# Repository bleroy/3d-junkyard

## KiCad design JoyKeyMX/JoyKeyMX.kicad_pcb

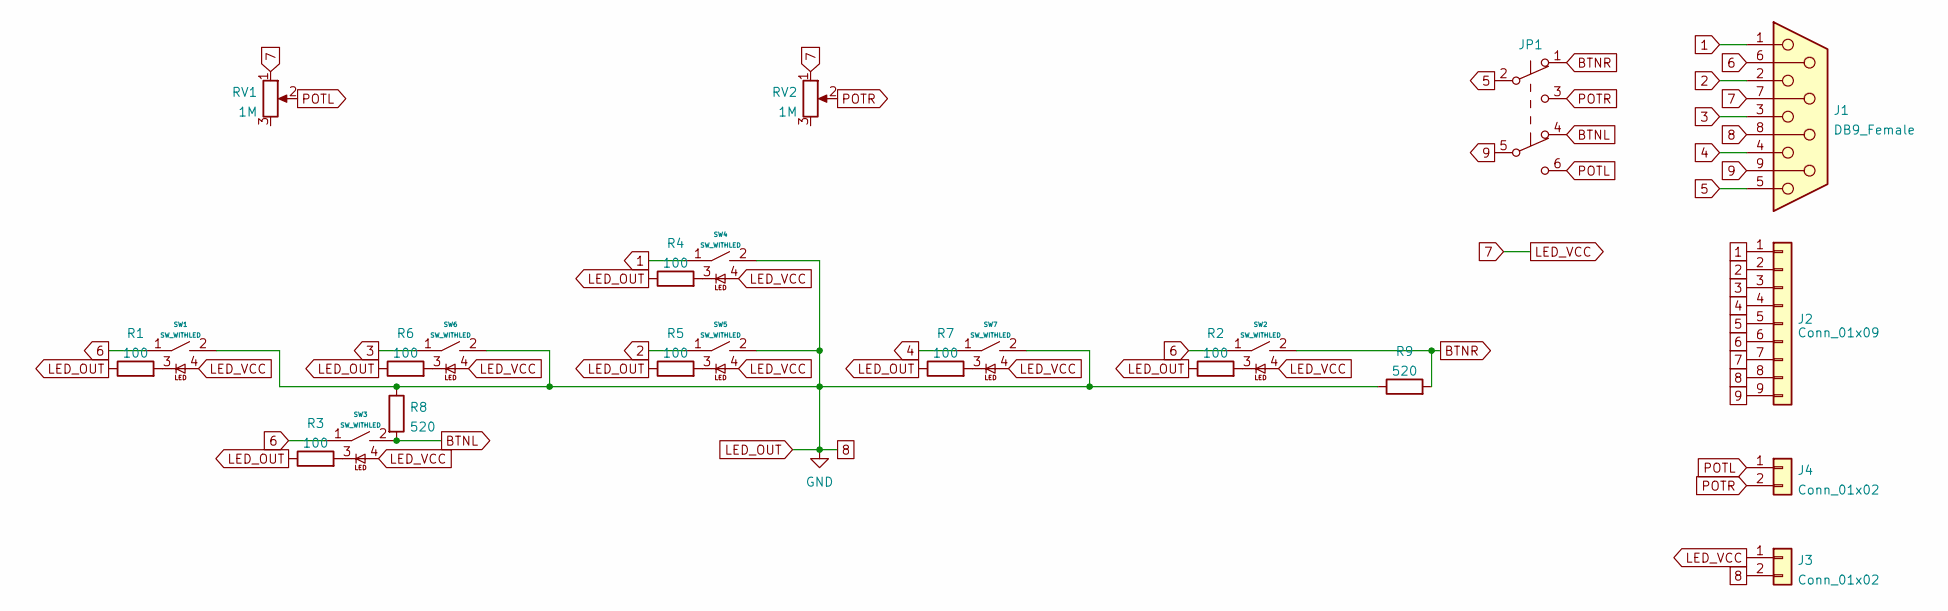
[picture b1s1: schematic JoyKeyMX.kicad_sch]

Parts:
J1: DB9_Female; DSUB-9_Female_Horizontal_P2.77x2.54mm_EdgePinOffset9.40mm
J2: Conn_01x09; PinHeader_1x09_P2.54mm_Vertical
J3, J4: Conn_01x02; PinHeader_1x02_P2.54mm_Vertical
JP1: DPDT; SW_CuK_JS202011AQN_DPDT_Angled
R1, R2, R3, R4, R5, R6, R7: 100; R_0603_1608Metric
R8, R9: 520; R_0603_1608Metric
RV1, RV2: 1M; Potentiometer (centered)
SW1, SW2, SW3, SW4, SW5, SW6, SW7: SW_WITHLED; MX-1-00U-LED

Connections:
1: J1.1, J2.1, SW4.1
2: J1.2, J2.2, SW5.1
3: J1.3, J2.3, SW6.1
4: J1.4, J2.4, SW7.1
5: J1.5, J2.5, JP1.2 (B)
6: J1.6, J2.6, SW1.1, SW2.1, SW3.1
7: J1.7, J2.7, J3.1, RV1.1, RV2.1, SW1.4, SW2.4, SW3.4, SW4.4, SW5.4, SW6.4, SW7.4
8: J1.8, J2.8, J3.2, R1.1, R2.1, R3.1, R4.1, R5.1, R6.1, R7.1, R8.1, R9.1, SW1.2, SW4.2, SW5.2, SW6.2, SW7.2
9: J1.9, J2.9, JP1.5 (B)
BTNL: JP1.4 (A), R8.2, SW3.2
BTNR: JP1.1 (A), R9.2, SW2.2
unnamed: R1.2, SW1.3
unnamed: R2.2, SW2.3
unnamed: R3.2, SW3.3
unnamed: R4.2, SW4.3
unnamed: R5.2, SW5.3
unnamed: R6.2, SW6.3
unnamed: R7.2, SW7.3
POTL: J4.1, JP1.6 (C), RV1.2
POTR: J4.2, JP1.3 (C), RV2.2

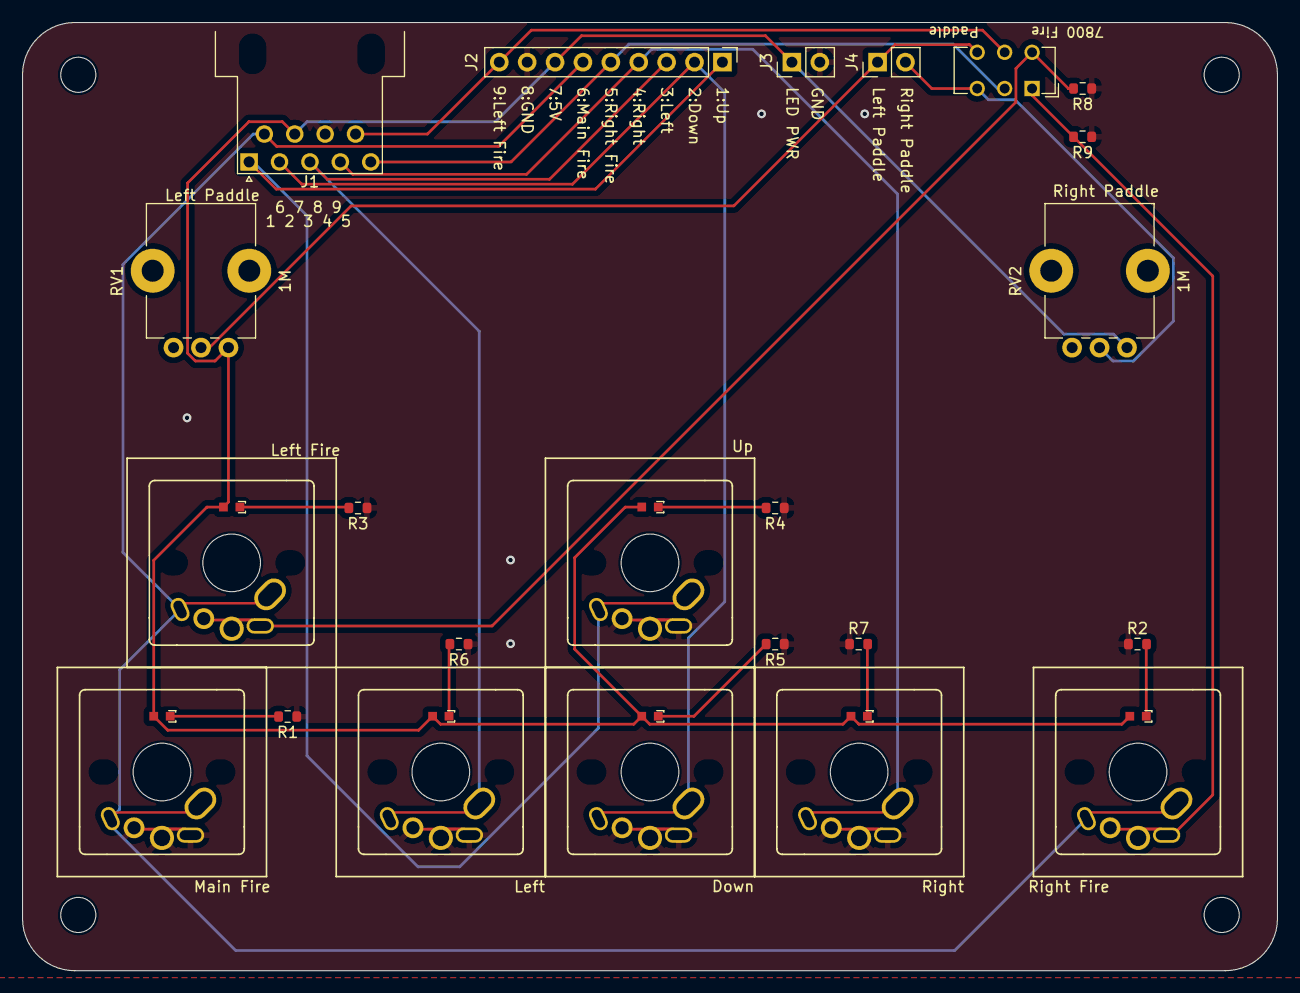
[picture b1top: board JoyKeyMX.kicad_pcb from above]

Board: 2 copper layers, 114.3 x 86.4 mm, 23 parts (0 on the bottom side), 20 nets.

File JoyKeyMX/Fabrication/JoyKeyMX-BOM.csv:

Comment,Designator,Footprint,JLCPCB Part #,Quantity
SW_WITHLED,"SW7,SW6,SW5,SW4,SW3,SW2,SW1",MX-1-00U-LED,C2297,7
560,"R9,R8",R_0603_1608Metric,C23204 ,2
100,"R7,R6,R5,R4,R3,R2,R1",R_0603_1608Metric,C22775,7
DPDT,JP1,SW_CuK_JS202011AQN_DPDT_Angled,,1
Conn_01x02,"J4,J3",PinHeader_1x02_P2.54mm_Vertical,,2
Conn_01x09,J2,PinHeader_1x09_P2.54mm_Vertical,,1
DB9_Female,J1,DSUB-9_Female_Horizontal_P2.77x2.54mm_EdgePinOffset9.40mm,,1
1M,"RV1,RV2",Potentiometer (centered),,2

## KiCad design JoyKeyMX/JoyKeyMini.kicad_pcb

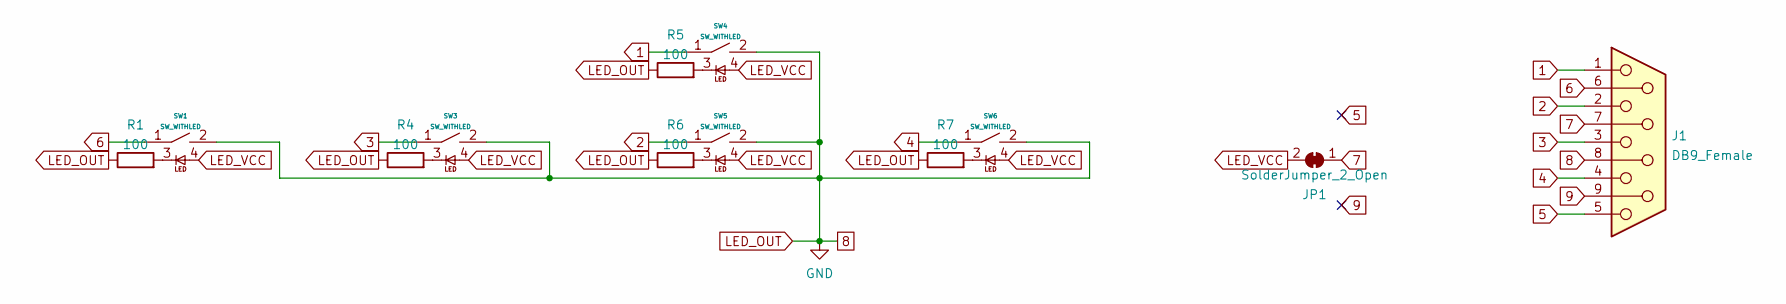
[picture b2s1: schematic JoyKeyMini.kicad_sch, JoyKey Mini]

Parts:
J1: DB9_Female; DSUB-9_Female_Horizontal_P2.77x2.54mm_EdgePinOffset9.40mm
JP1: SolderJumper_2_Open; SolderJumper-2_P1.3mm_Open_RoundedPad1.0x1.5mm
R1, R4, R5, R6, R7: 100; R_0603_1608Metric_Pad0.98x0.95mm_HandSolder
SW1, SW3, SW4, SW5, SW6: SW_WITHLED; MX-1-00U-LED

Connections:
1: J1.1, SW4.1
2: J1.2, SW5.1
3: J1.3, SW3.1
4: J1.4, SW6.1
5: J1.5
6: J1.6, SW1.1
7: J1.7, JP1.1 (A)
8: J1.8, R1.1, R4.1, R5.1, R6.1, R7.1, SW1.2, SW3.2, SW4.2, SW5.2, SW6.2
9: J1.9
LED_VCC: JP1.2 (B), SW1.4, SW3.4, SW4.4, SW5.4, SW6.4
unnamed: R1.2, SW1.3
unnamed: R4.2, SW3.3
unnamed: R5.2, SW4.3
unnamed: R6.2, SW5.3
unnamed: R7.2, SW6.3

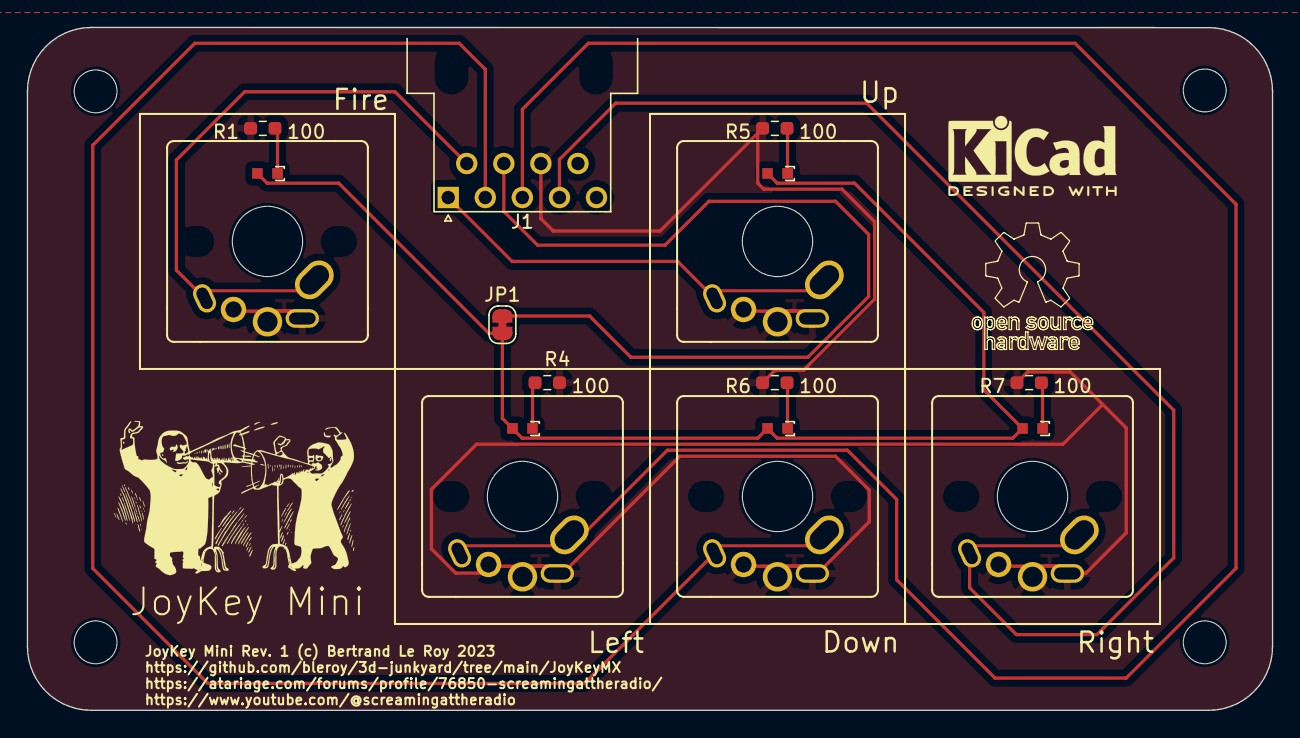
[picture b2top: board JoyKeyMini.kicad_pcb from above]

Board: 2 copper layers, 93.0 x 51.0 mm, 12 parts (0 on the bottom side), 13 nets.

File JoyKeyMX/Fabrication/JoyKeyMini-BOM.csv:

Comment,Designator,Footprint,Quantity,Designation,JCLPCB part #
SMD LED mounted on switch footprint,"SW1,SW6,SW4,SW5,SW3",MX-1-00U-LED,5,SW_WITHLED,C193191
SMD Resistor,"R7,R6,R5,R4,R1",R_0603_1608Metric_Pad0.98x0.95mm_HandSolder,5,100,C22775

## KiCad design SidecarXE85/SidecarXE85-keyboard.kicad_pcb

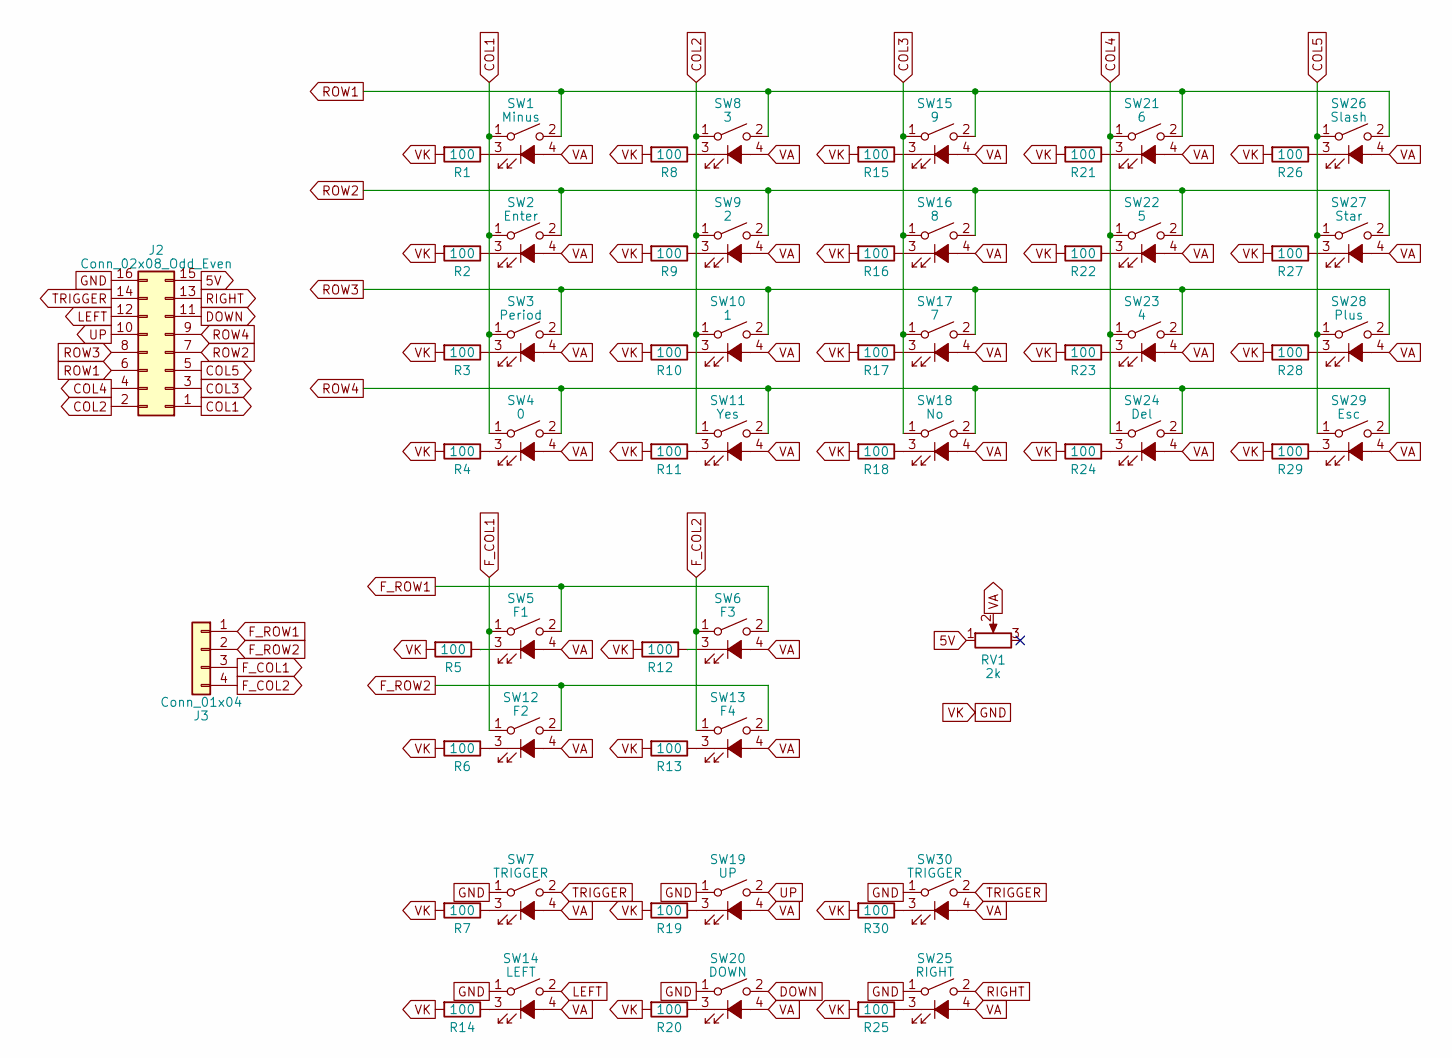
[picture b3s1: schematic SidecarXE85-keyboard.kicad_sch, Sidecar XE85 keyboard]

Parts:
J2: Conn_02x08_Odd_Even; IDC-Header_2x08_P2.54mm_Horizontal
J3: Conn_01x04; JST_EH_S4B-EH_1x04_P2.50mm_Horizontal
R1, R2, R3, R4, R5, R6, R7, R8, R9, R10, R11, R12, R13, R14, R15, R16, R17, R18, R19, R20, R21, R22, R23, R24, R25, R26, R27, R28, R29, R30: 100; R_0603_1608Metric
RV1: 2k; Potentiometer_Piher_PT-6-V_Vertical
SW1: Minus; MX-1-00U-LED
SW2: Enter; MX-2-00U-VERT-LED
SW3: Period; MX-1-00U-LED
SW4: 0; MX-2-00U-LED
SW5: F1; MX-1-50U-Atari-Fn-LED
SW6: F3; MX-1-50U-Atari-Fn-LED
SW7, SW30: TRIGGER; MX-1-00U-LED
SW8: 3; MX-1-00U-LED
SW9: 2; MX-1-00U-LED
SW10: 1; MX-1-00U-LED
SW11: Yes; MX-1-00U-LED
SW12: F2; MX-1-50U-Atari-Fn-LED
SW13: F4; MX-1-50U-Atari-Fn-LED
SW14: LEFT; MX-1-00U-LED
SW15: 9; MX-1-00U-LED
SW16: 8; MX-1-00U-LED
SW17: 7; MX-1-00U-LED
SW18: No; MX-1-00U-LED
SW19: UP; MX-1-00U-LED
SW20: DOWN; MX-1-00U-LED
SW21: 6; MX-1-00U-LED
SW22: 5; MX-1-00U-LED
SW23: 4; MX-1-00U-LED
SW24: Del; MX-1-50U-LED
SW25: RIGHT; MX-1-00U-LED
SW26: Slash; MX-1-00U-LED
SW27: Star; MX-1-00U-LED
SW28: Plus; MX-1-00U-LED
SW29: Esc; MX-1-50U-LED

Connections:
5V: J2.15, RV1.1
COL1: J2.1, SW1.1, SW2.1, SW3.1, SW4.1
COL2: J2.2, SW8.1, SW9.1, SW10.1, SW11.1
COL3: J2.3, SW15.1, SW16.1, SW17.1, SW18.1
COL4: J2.4, SW21.1, SW22.1, SW23.1, SW24.1
COL5: J2.5, SW26.1, SW27.1, SW28.1, SW29.1
DOWN: J2.11, SW20.2
F_COL1: J3.3, SW5.1, SW12.1
F_COL2: J3.4, SW6.1, SW13.1
F_ROW1: J3.1, SW5.2, SW6.2
F_ROW2: J3.2, SW12.2, SW13.2
GND: J2.16, R1.2, R2.2, R3.2, R4.2, R5.2, R6.2, R7.2, R8.2, R9.2, R10.2, R11.2, R12.2, R13.2, R14.2, R15.2, R16.2, R17.2, R18.2, R19.2, R20.2, R21.2, R22.2, R23.2, R24.2, R25.2, R26.2, R27.2, R28.2, R29.2, R30.2, SW7.1, SW14.1, SW19.1, SW20.1, SW25.1, SW30.1
LEFT: J2.12, SW14.2
unnamed: R1.1, SW1.3 (K)
unnamed: R2.1, SW2.3 (K)
unnamed: R3.1, SW3.3 (K)
unnamed: R4.1, SW4.3 (K)
unnamed: R5.1, SW5.3 (K)
unnamed: R12.1, SW6.3 (K)
unnamed: R7.1, SW7.3 (K)
unnamed: R8.1, SW8.3 (K)
unnamed: R9.1, SW9.3 (K)
unnamed: R10.1, SW10.3 (K)
unnamed: R11.1, SW11.3 (K)
unnamed: R6.1, SW12.3 (K)
unnamed: R13.1, SW13.3 (K)
unnamed: R14.1, SW14.3 (K)
unnamed: R15.1, SW15.3 (K)
unnamed: R16.1, SW16.3 (K)
unnamed: R17.1, SW17.3 (K)
unnamed: R18.1, SW18.3 (K)
unnamed: R19.1, SW19.3 (K)
unnamed: R20.1, SW20.3 (K)
unnamed: R21.1, SW21.3 (K)
unnamed: R22.1, SW22.3 (K)
unnamed: R23.1, SW23.3 (K)
unnamed: R24.1, SW24.3 (K)
unnamed: R25.1, SW25.3 (K)
unnamed: R26.1, SW26.3 (K)
unnamed: R27.1, SW27.3 (K)
unnamed: R28.1, SW28.3 (K)
unnamed: R29.1, SW29.3 (K)
unnamed: R30.1, SW30.3 (K)
RIGHT: J2.13, SW25.2
ROW1: J2.6, SW1.2, SW8.2, SW15.2, SW21.2, SW26.2
ROW2: J2.7, SW2.2, SW9.2, SW16.2, SW22.2, SW27.2
ROW3: J2.8, SW3.2, SW10.2, SW17.2, SW23.2, SW28.2
ROW4: J2.9, SW4.2, SW11.2, SW18.2, SW24.2, SW29.2
TRIGGER: J2.14, SW7.2, SW30.2
UP: J2.10, SW19.2
VA: RV1.2, SW1.4 (A), SW2.4 (A), SW3.4 (A), SW4.4 (A), SW5.4 (A), SW6.4 (A), SW7.4 (A), SW8.4 (A), SW9.4 (A), SW10.4 (A), SW11.4 (A), SW12.4 (A), SW13.4 (A), SW14.4 (A), SW15.4 (A), SW16.4 (A), SW17.4 (A), SW18.4 (A), SW19.4 (A), SW20.4 (A), SW21.4 (A), SW22.4 (A), SW23.4 (A), SW24.4 (A), SW25.4 (A), SW26.4 (A), SW27.4 (A), SW28.4 (A), SW29.4 (A), SW30.4 (A)

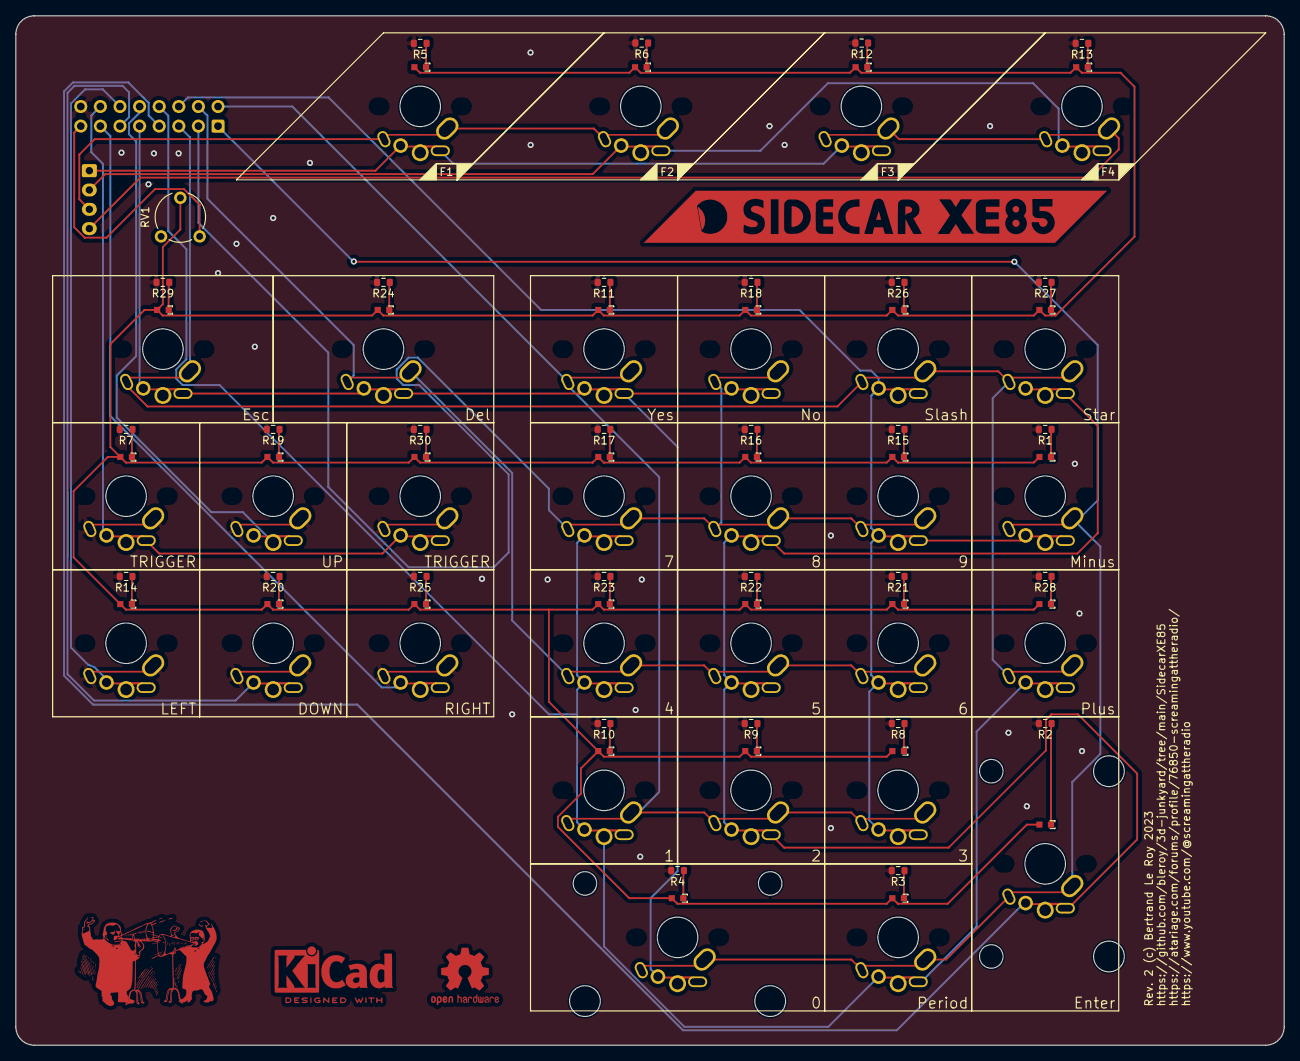
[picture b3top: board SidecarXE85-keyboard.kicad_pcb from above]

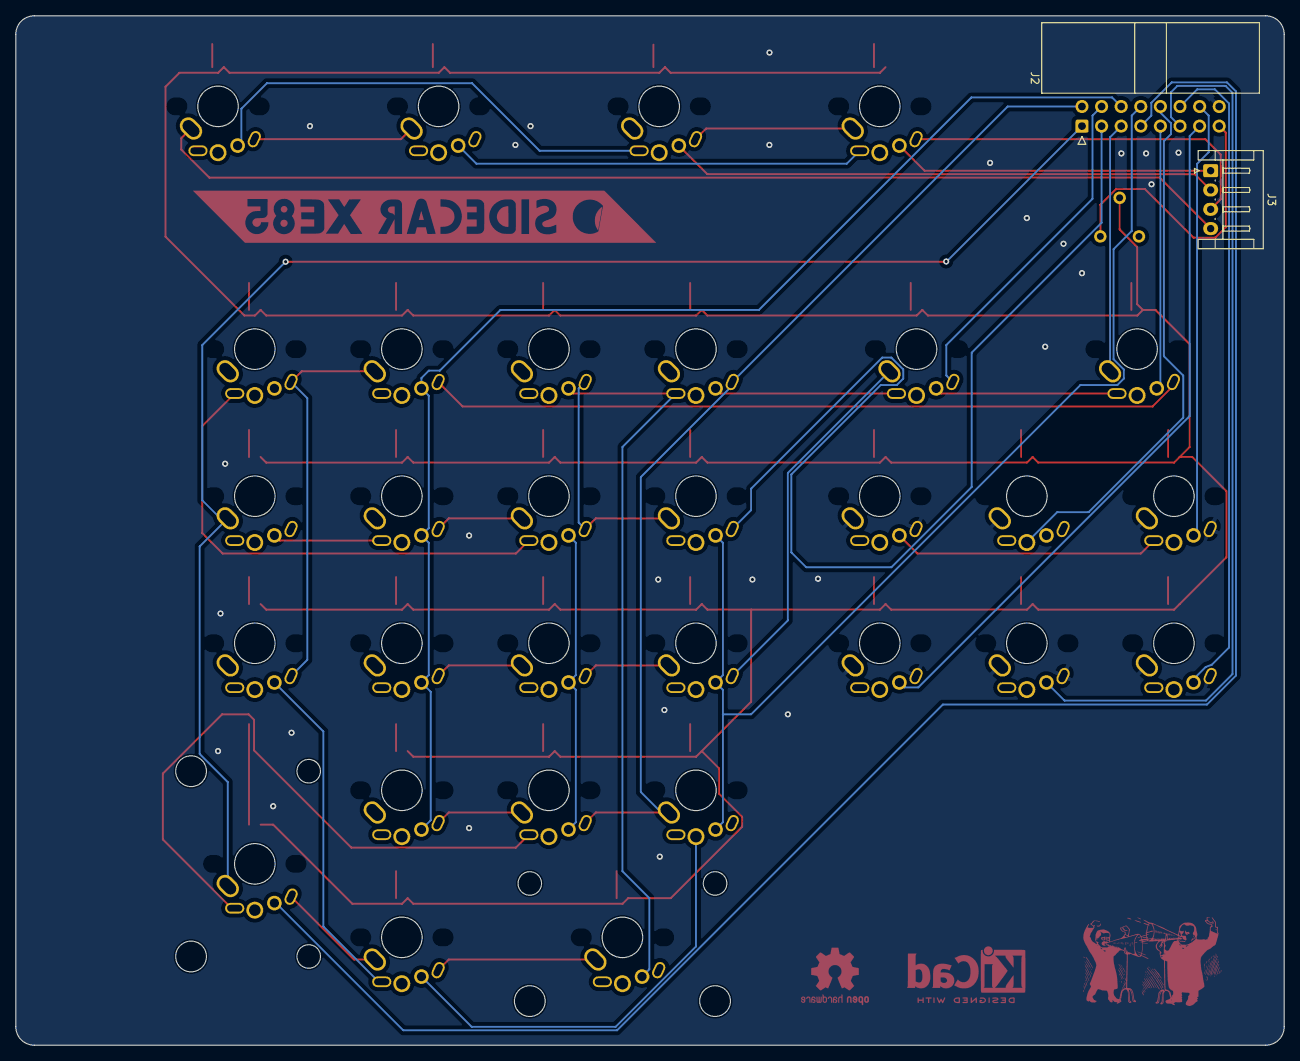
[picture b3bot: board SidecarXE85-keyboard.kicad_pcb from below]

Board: 2 copper layers, 164.3 x 133.4 mm, 63 parts (2 on the bottom side), 51 nets.

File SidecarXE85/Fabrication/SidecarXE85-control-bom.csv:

Designator,Footprint,Quantity,Value,LCSC Part #
J2,TE_Micro-MaTch_1-215079-8_2x09_P1.27mm_Vertical,1,Conn_02x09_Odd_Even,
J3,JST_EH_S4B-EH_1x04_P2.50mm_Horizontal,1,Conn_01x04,
"R1, R10, R11, R12, R13, R14, R15, R16, R17, R18, R19, R2, R20, R21, R22, R23, R24, R25, R26, R27, R28, R29, R3, R30, R4, R5, R6, R7, R8, R9",603,30,100,C22775 
RV1,Potentiometer_Piher_PT-6-V_Vertical,1,2k,
RV2,Potentiometer_Bourns_PTV09A-1_Single_Vertical,1,1M,
SW1,MX-1-00U-LED,1,Minus,C193191
SW10,MX-1-00U-LED,1,1,C193191
SW11,MX-1-00U-LED,1,Yes,C193191
SW12,MX-1-50U-Atari-Fn-LED,1,F2,C193191
SW13,MX-1-50U-Atari-Fn-LED,1,F4,C193191
SW14,MX-1-00U-LED,1,LEFT,C193191
SW15,MX-1-00U-LED,1,9,C193191
SW16,MX-1-00U-LED,1,8,C193191
SW17,MX-1-00U-LED,1,7,C193191
SW18,MX-1-00U-LED,1,No,C193191
SW19,MX-1-00U-LED,1,UP,C193191
SW2,MX-2-00U-VERT-LED,1,Enter,C193191
SW20,MX-1-00U-LED,1,DOWN,C193191
SW21,MX-1-00U-LED,1,6,C193191
SW22,MX-1-00U-LED,1,5,C193191
SW23,MX-1-00U-LED,1,4,C193191
SW24,MX-1-50U-LED,1,Del,C193191
SW25,MX-1-00U-LED,1,RIGHT,C193191
SW26,MX-1-00U-LED,1,Slash,C193191
SW27,MX-1-00U-LED,1,Star,C193191
SW28,MX-1-00U-LED,1,Plus,C193191
SW29,MX-1-50U-LED,1,Esc,C193191
SW3,MX-1-00U-LED,1,Period,C193191
"SW30, SW7",MX-1-00U-LED,2,TRIGGER,C193191
SW4,MX-2-00U-LED,1,0,C193191
SW5,MX-1-50U-Atari-Fn-LED,1,F1,C193191
SW6,MX-1-50U-Atari-Fn-LED,1,F3,C193191
SW8,MX-1-00U-LED,1,3,C193191
SW9,MX-1-00U-LED,1,2,C193191

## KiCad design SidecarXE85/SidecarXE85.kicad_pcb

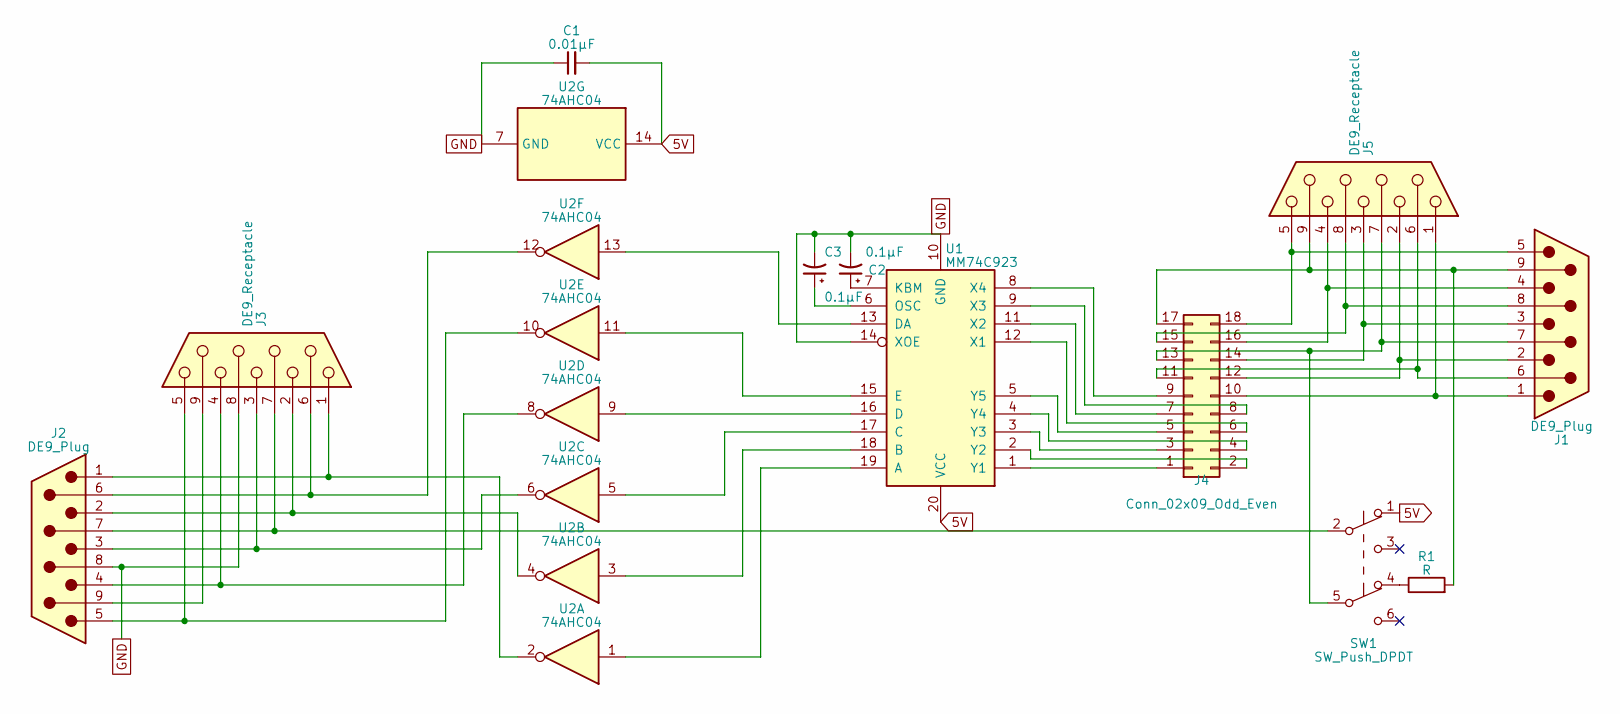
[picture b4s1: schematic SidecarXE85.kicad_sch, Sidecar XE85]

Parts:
C1: 0.01µF; C_Disc_D5.0mm_W2.5mm_P5.00mm
C2, C3: 0.1µF; C_Disc_D5.0mm_W2.5mm_P5.00mm
J1, J2: DE9_Plug; DSUB-9_Female_Horizontal_P2.77x2.84mm_EdgePinOffset9.90mm_H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
J3, J5: DE9_Receptacle; DSUB-9_Male_Horizontal_P2.77x2.84mm_EdgePinOffset9.90mm_Hou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
J4: Conn_02x09_Odd_Even; TE_Micro-MaTch_1-215079-8_2x09_P1.27mm_Vertical
R1: R; R_Axial_DIN0207_L6.3mm_D2.5mm_P10.16mm_Horizontal
SW1: SW_Push_DPDT; SW_CuK_JS202011AQN_DPDT_Angled
U1: MM74C923; DIP-20_W7.62mm_Socket
U2: 74AHC04; DIP-14_W7.62mm_Socket

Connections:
5V: C1.2, SW1.1 (A), U1.20 (VCC), U2.14 (VCC)
GND: C1.1, C2.2, C3.2, J2.8, J3.8, U1.10 (GND), U1.14 (XOE), U2.7 (GND)
unnamed: J2.1, J3.1, U2.2
unnamed: J2.2, J3.2, U2.4
unnamed: J2.3, J3.3, U2.6
unnamed: J2.4, J3.4, U2.8
unnamed: J2.5, J3.5, U2.10
unnamed: J2.6, J3.6, U2.12
unnamed: J2.7, J3.7, SW1.2 (B)
unnamed: J2.9, J3.9
unnamed: J4.1, U1.1 (Y1)
unnamed: J4.2, U1.2 (Y2)
unnamed: J4.3, U1.3 (Y3)
unnamed: J4.4, U1.4 (Y4)
unnamed: J4.5, U1.5 (Y5)
unnamed: J4.6, U1.12 (X1)
unnamed: J4.7, U1.11 (X2)
unnamed: J4.8, U1.9 (X3)
unnamed: J4.9, U1.8 (X4)
unnamed: J1.1, J4.10, J5.1
unnamed: J1.6, J4.11, J5.6
unnamed: J1.2, J4.12, J5.2
unnamed: J1.7, J4.13, J5.7, SW1.5 (B)
unnamed: J1.3, J4.14, J5.3
unnamed: J1.8, J4.15, J5.8
unnamed: J1.4, J4.16, J5.4
unnamed: J1.9, J4.17, J5.9, R1.2
unnamed: J1.5, J4.18, J5.5
unnamed: R1.1, SW1.4 (A)
unnamed: U1.19 (A), U2.1
unnamed: U1.18 (B), U2.3
unnamed: U1.17 (C), U2.5
unnamed: U1.16 (D), U2.9
unnamed: U1.13 (DA), U2.13
unnamed: U1.15 (E), U2.11
unnamed: C2.1, U1.7 (KBM)
unnamed: C3.1, U1.6 (OSC)

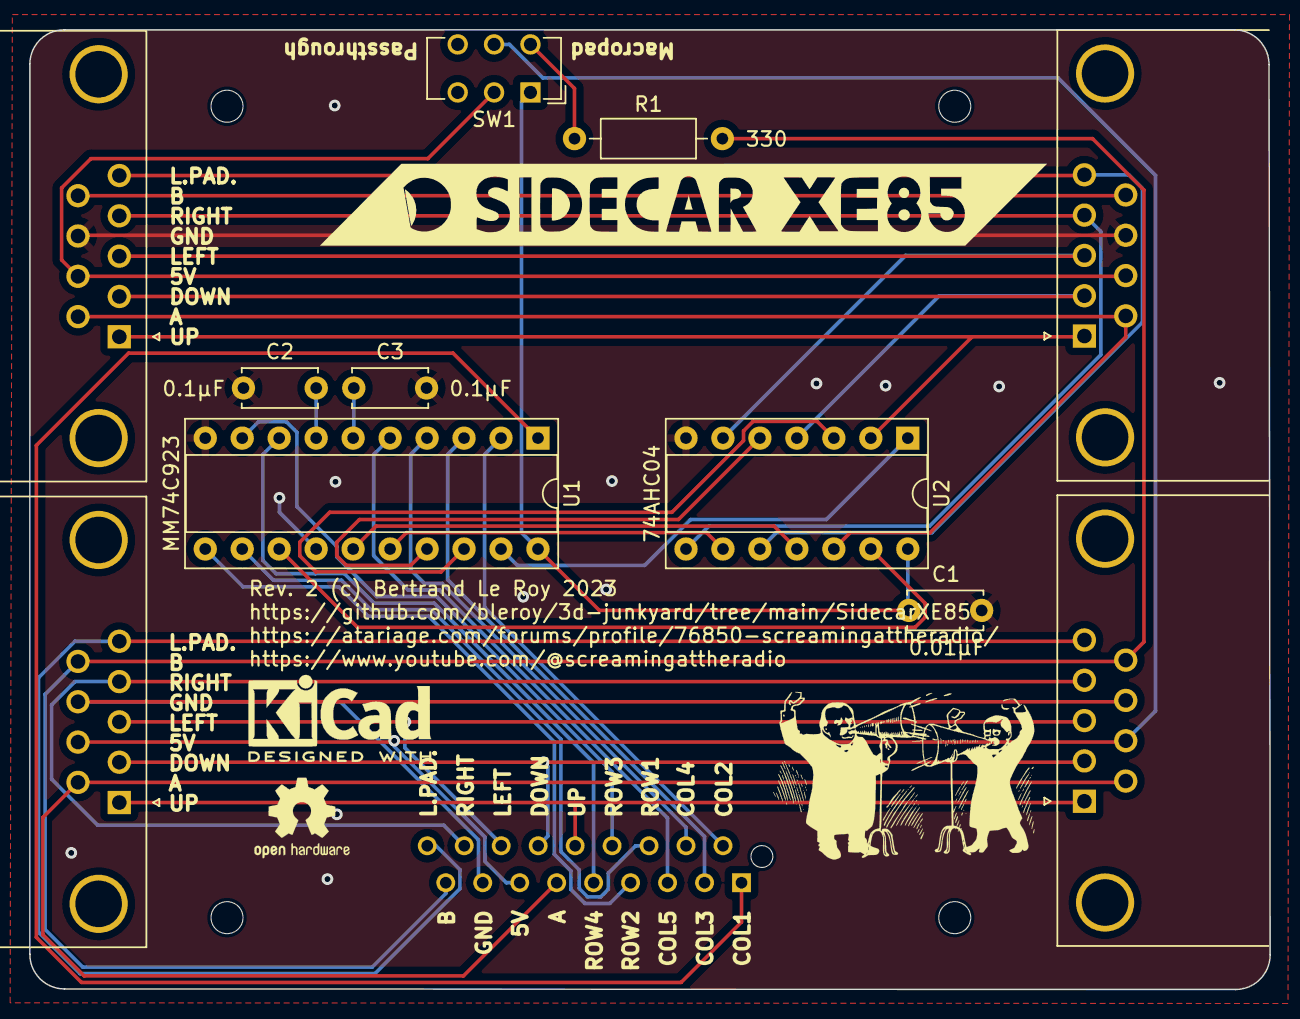
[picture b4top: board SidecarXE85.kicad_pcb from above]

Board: 2 copper layers, 85.2 x 65.9 mm, 12 parts (1 on the bottom side), 37 nets.

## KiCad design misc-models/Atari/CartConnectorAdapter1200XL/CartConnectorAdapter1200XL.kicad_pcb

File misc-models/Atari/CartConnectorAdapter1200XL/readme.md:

# Replacement cartridge connector for ATARI 1200XL computers

The Atari 1200XL's cartridge port is quite unique: it's basically a tunnel, made of three plastic parts around an angled edge connector that's impossible to source as a new part.

If you need to replace a damaged connector or mount one on a new board, you need something like this board and printed parts.

## Bill of materials

To build a new cartridge port, you'll need:

* 1x [Printed connector holder](../CartridgeConnectorHolder1200XL.stl)
* 1x [Printed cartridge port](../CartridgePort1200XL.stl)
* 1x [Adapter PCB](./production/CartConnectorAdapter1200XL.zip) - Order in 1mm thickness
* 1x [Angled 2x15 edge connector](https://www.aliexpress.us/item/2255800960638500.html)
* 2x [15pin 15mm tall 2.54mm pitch headers](https://www.aliexpress.us/item/3256801327743339.html)
* 2x [15pin 2.54mm pitch header sockets](https://www.aliexpress.us/item/2255801012106911.html)

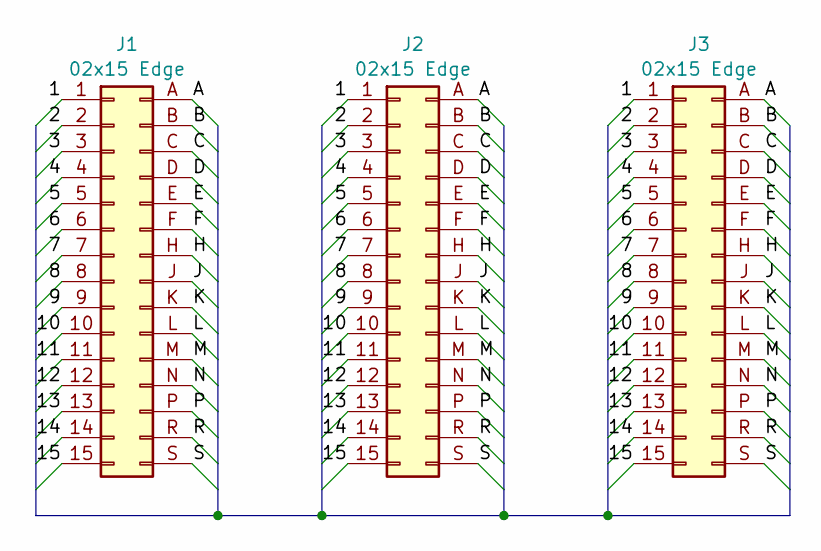
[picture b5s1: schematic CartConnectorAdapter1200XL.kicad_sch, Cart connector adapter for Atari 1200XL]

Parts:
J1, J2: 02x15 Edge; Atari_Cartridge_Connector
J3: 02x15 Edge; PinHeader_2x15_P2.54mm_Vertical

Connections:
/1: J1.1, J2.1, J3.1
/2: J1.2, J2.2, J3.2
/3: J1.3, J2.3, J3.3
/4: J1.4, J2.4, J3.4
/5: J1.5, J2.5, J3.5
/6: J1.6, J2.6, J3.6
/7: J1.7, J2.7, J3.7
/8: J1.8, J2.8, J3.8
/9: J1.9, J2.9, J3.9
/10: J1.10, J2.10, J3.10
/11: J1.11, J2.11, J3.11
/12: J1.12, J2.12, J3.12
/13: J1.13, J2.13, J3.13
/14: J1.14, J2.14, J3.14
/15: J1.15, J2.15, J3.15
/A: J1.A (Pin_16), J2.A (Pin_16), J3.A (Pin_16)
/B: J1.B (Pin_17), J2.B (Pin_17), J3.B (Pin_17)
/C: J1.C (Pin_18), J2.C (Pin_18), J3.C (Pin_18)
/D: J1.D (Pin_19), J2.D (Pin_19), J3.D (Pin_19)
/E: J1.E (Pin_20), J2.E (Pin_20), J3.E (Pin_20)
/F: J1.F (Pin_21), J2.F (Pin_21), J3.F (Pin_21)
/H: J1.H (Pin_22), J2.H (Pin_22), J3.H (Pin_22)
/J: J1.J (Pin_23), J2.J (Pin_23), J3.J (Pin_23)
/K: J1.K (Pin_24), J2.K (Pin_24), J3.K (Pin_24)
/L: J1.L (Pin_25), J2.L (Pin_25), J3.L (Pin_25)
/M: J1.M (Pin_26), J2.M (Pin_26), J3.M (Pin_26)
/N: J1.N (Pin_27), J2.N (Pin_27), J3.N (Pin_27)
/P: J1.P (Pin_28), J2.P (Pin_28), J3.P (Pin_28)
/R: J1.R (Pin_29), J2.R (Pin_29), J3.R (Pin_29)
/S: J1.S (Pin_30), J2.S (Pin_30), J3.S (Pin_30)

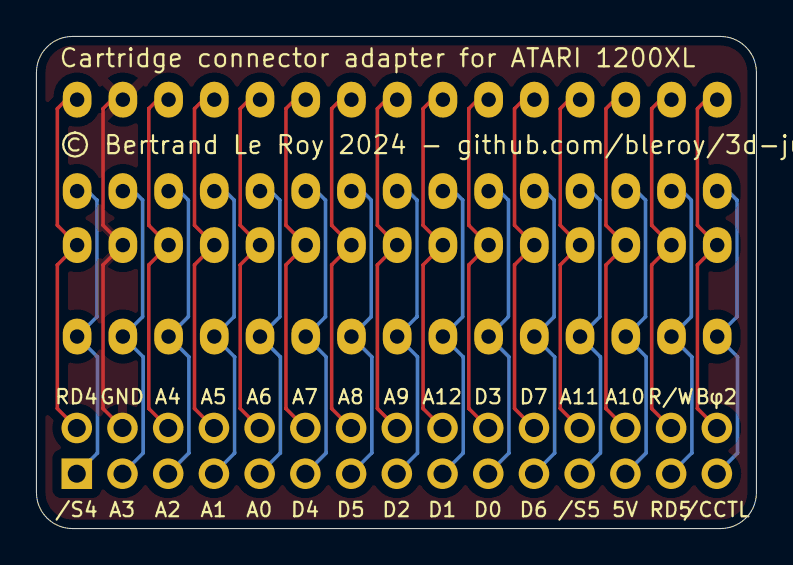
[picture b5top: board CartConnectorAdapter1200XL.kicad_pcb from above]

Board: 2 copper layers, 40.0 x 27.3 mm, 3 parts (0 on the bottom side), 30 nets.

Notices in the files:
misc-models/Atari/CartConnectorAdapter1200XL/CartConnectorAdapter1200XL.kicad_pcb:
© Bertrand Le Roy 2024 - github.com/bleroy/3d-junkyard
